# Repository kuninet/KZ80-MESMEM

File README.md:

# KZ80シリーズ用 偽MSX1 専用メモリーボード

## 概要

* KZ80-CPUBなどを使って偽MSX1を構成するためのメモリーボードです。
* メモリーICのチップセレクト信号は、[KZ80-MSXCTRG](https://github.com/kuninet/KZ80-MSXCTRG)ボードに載っているMSXスロット信号で制御します。かならずペアで使用してください。

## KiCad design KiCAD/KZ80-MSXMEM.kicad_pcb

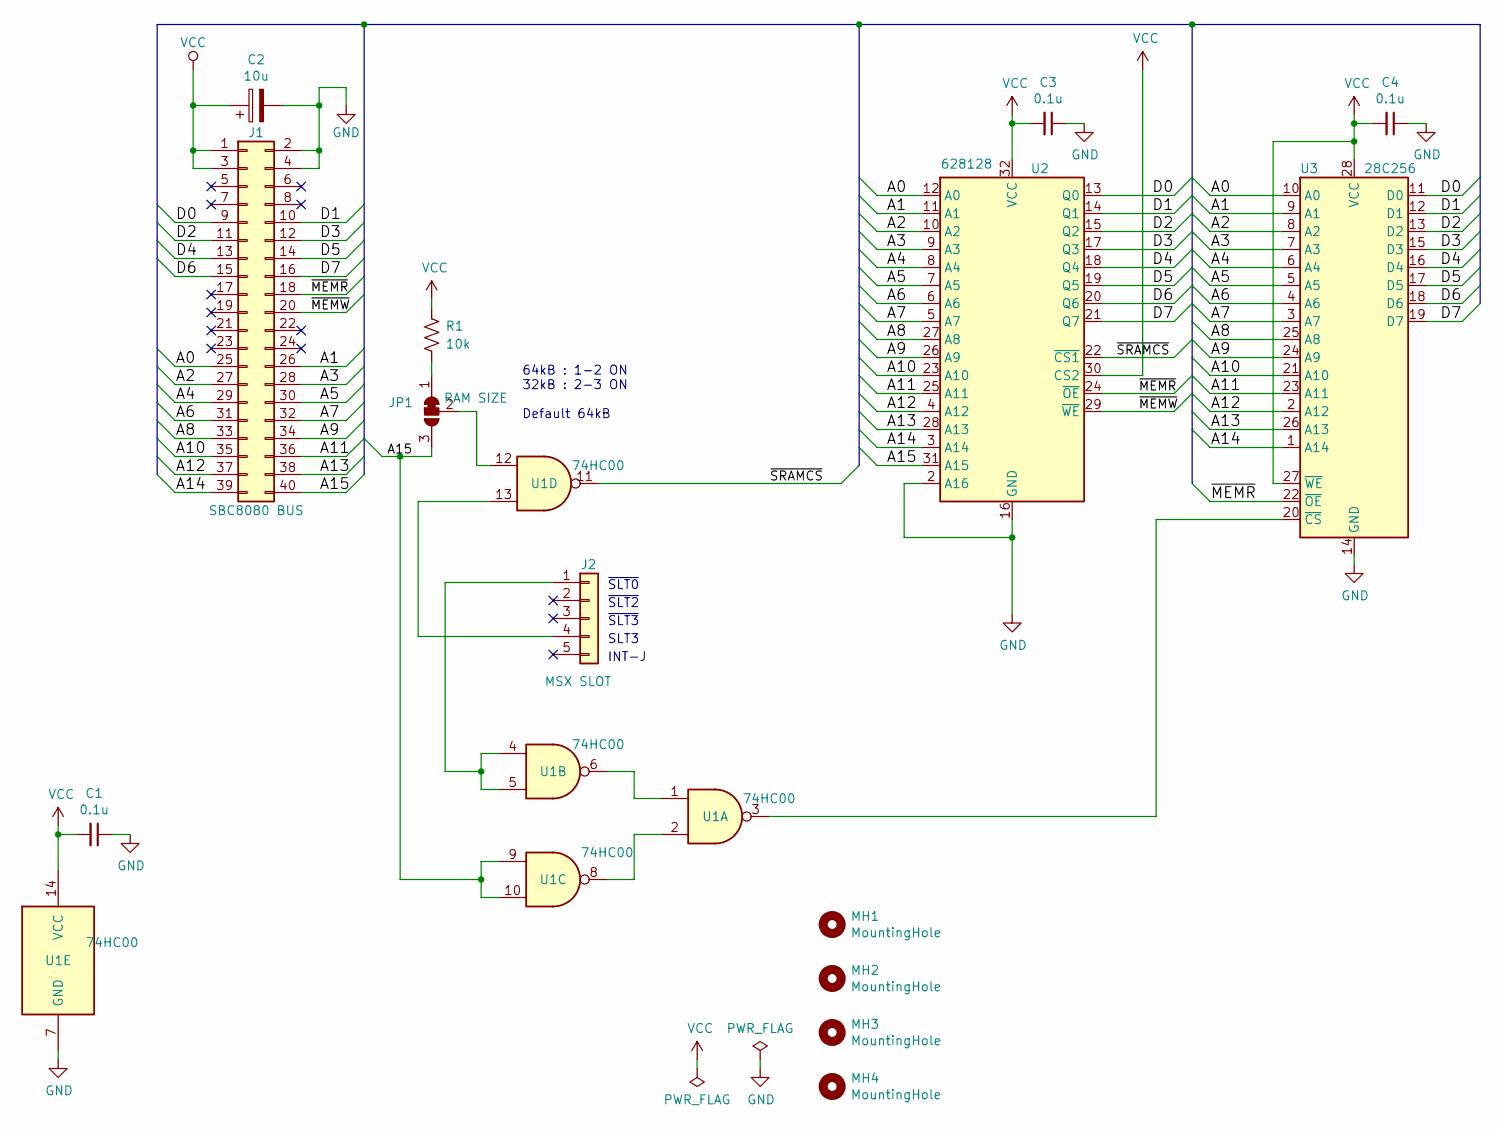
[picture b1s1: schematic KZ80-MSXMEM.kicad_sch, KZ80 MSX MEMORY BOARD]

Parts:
C1, C3, C4: 0.1u; C_Disc_D3.0mm_W1.6mm_P2.50mm
C2: 10u; CP_Radial_D5.0mm_P2.50mm
J1: SBC8080 BUS; PinHeader_2x20_P2.54mm_Horizontal
J2: MSX SLOT; PinHeader_1x05_P2.54mm_Horizontal
JP1: RAM SIZE
MH1, MH2, MH3, MH4: MountingHole; MountingHole_3.2mm_M3
R1: 10k
U1: 74HC00; DIP-14_W7.62mm_Socket_LongPads
U2: 628128
U3: 28C256; DIP-28_W15.24mm_Socket_LongPads

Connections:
/A0: J1.25, U2.12 (A0), U3.10 (A0)
/A1: J1.26, U2.11 (A1), U3.9 (A1)
/A2: J1.27, U2.10 (A2), U3.8 (A2)
/A3: J1.28, U2.9 (A3), U3.7 (A3)
/A4: J1.29, U2.8 (A4), U3.6 (A4)
/A5: J1.30, U2.7 (A5), U3.5 (A5)
/A6: J1.31, U2.6 (A6), U3.4 (A6)
/A7: J1.32, U2.5 (A7), U3.3 (A7)
/A8: J1.33, U2.27 (A8), U3.25 (A8)
/A9: J1.34, U2.26 (A9), U3.24 (A9)
/A10: J1.35, U2.23 (A10), U3.21 (A10)
/A11: J1.36, U2.25 (A11), U3.23 (A11)
/A12: J1.37, U2.4 (A12), U3.2 (A12)
/A13: J1.38, U2.28 (A13), U3.26 (A13)
/A14: J1.39, U2.3 (A14), U3.1 (A14)
/A15: J1.40, JP1.3 (B), U1.9, U1.10, U2.31 (A15)
/D0: J1.9, U2.13 (Q0), U3.11 (D0)
/D1: J1.10, U2.14 (Q1), U3.12 (D1)
/D2: J1.11, U2.15 (Q2), U3.13 (D2)
/D3: J1.12, U2.17 (Q3), U3.15 (D3)
/D4: J1.13, U2.18 (Q4), U3.16 (D4)
/D5: J1.14, U2.19 (Q5), U3.17 (D5)
/D6: J1.15, U2.20 (Q6), U3.18 (D6)
/D7: J1.16, U2.21 (Q7), U3.19 (D7)
/~MEMR: J1.18, U2.24 (~OE), U3.22 (~OE)
/~MEMW: J1.20, U2.29 (~WE)
/~SRAMCS: U1.11, U2.22 (~CS1)
GND: C1.1, C2.2, C3.1, C4.1, J1.2, J1.4, U1.7 (GND), U2.2 (A16), U2.16 (GND), U3.14 (GND)
unnamed: J2.1, U1.4, U1.5
unnamed: J2.4, U1.13
unnamed: JP1.1 (A), R1.2
unnamed: JP1.2 (C), U1.12
unnamed: U1.1, U1.6
unnamed: U1.2, U1.8
unnamed: U1.3, U3.20 (~CS)
VCC: C1.2, C2.1, C3.2, C4.2, J1.1, J1.3, R1.1, U1.14 (VCC), U2.30 (CS2), U2.32 (VCC), U3.27 (~WE), U3.28 (VCC)

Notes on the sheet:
~{SLT3}
~{SLT2}
SLT3
INT-J
~{SLT0}
64kB : 1-2 ON 32kB : 2-3 ON Default 64kB

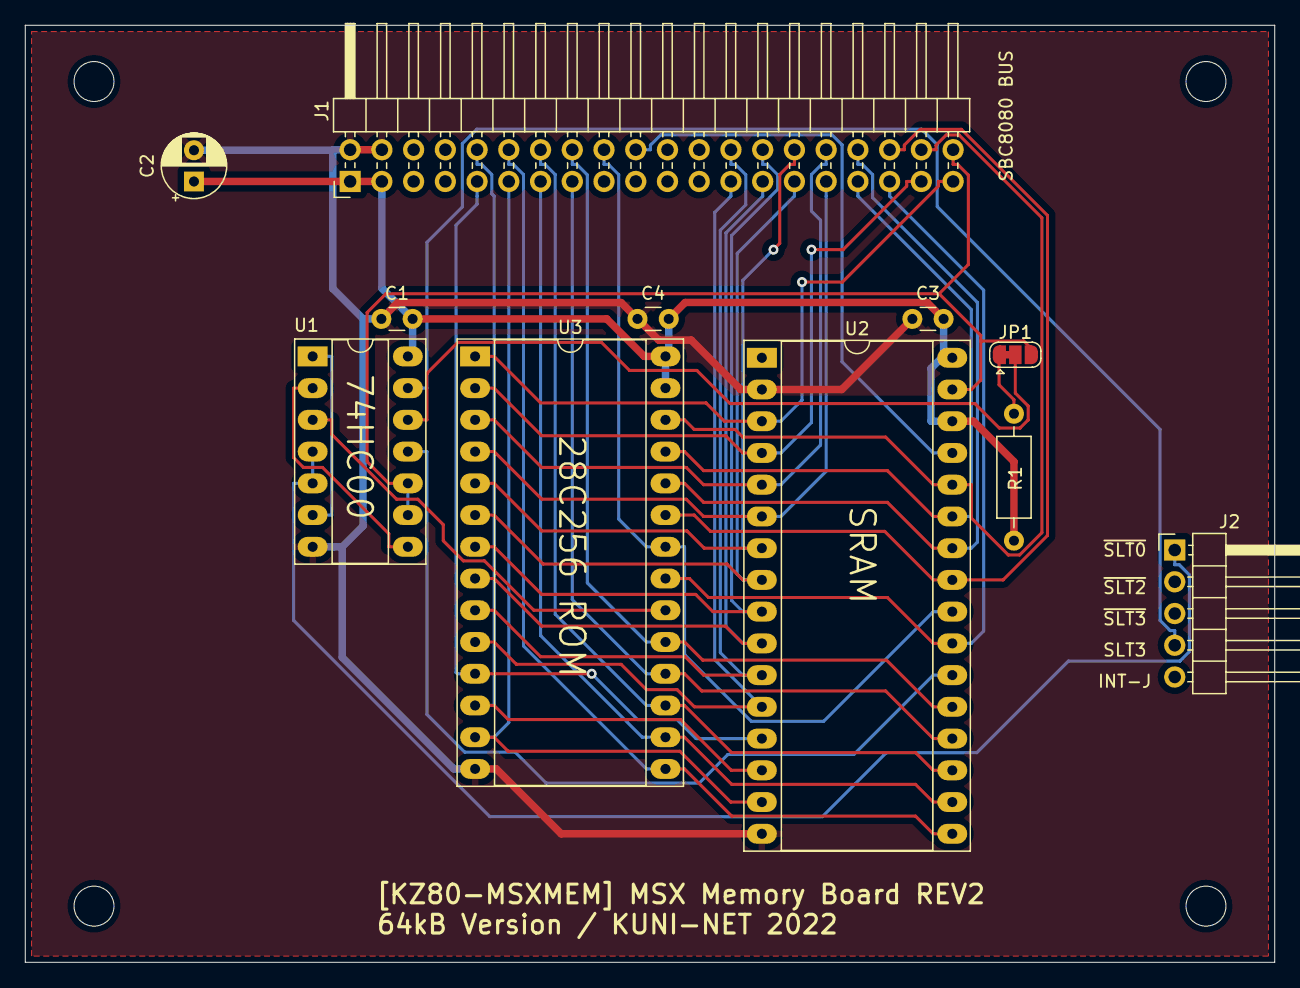
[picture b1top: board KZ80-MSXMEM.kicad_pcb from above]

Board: 2 copper layers, 100.0 x 75.0 mm, 15 parts (0 on the bottom side), 36 nets.

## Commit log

2021-12-18 init
2021-12-18 README追加など
2021-12-18 Create LICENSE
2022-11-05 REV2 64kB Version ガーバー出力
2022-11-05 REV2 ガーバー再出力
2024-04-28 部品表 追加
